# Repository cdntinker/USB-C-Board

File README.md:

# The NerdMage Rabbit Stack  Project

**_This project Will likely ALWAYS be a WIP._**

Do keep in mind that, because this project is continuously evolving, it'd be a very good idea to verify that any board you have an interest in is complete enough to meet your needs BEFORE having it fabbed.

The basic concept is a USB-C PD-capable power input section for various projects.  The initial board design & format is based on an ongoing project where 34x34mm is the maximum available space for this portion of the design.

In fact, the first USB power board for that project was 35x26mm & a photo of it is [in the Pix folder here](Pix/The-Original.png).  You can see that it was a very minimal USB-C to 3v3 power supply.

Now...

Many rabbit-holes later...

Many, many rabbit-holes later...

Things may be getting a little out of hand...

---

## 2023/09/29
Redesignating this repo from "USB-C-Board" to "The NerdMage Rabbit Stack".

## 2024/03/01
Re-arranging the hardware files for better clarity.

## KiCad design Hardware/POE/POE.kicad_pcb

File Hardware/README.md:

# The NerdMage Rabbit Stack  Project

* KiCAD Customs
  * Customised symbols, footprints & 3D models for KiCAD
* 3D
  * 3D render models & such
  * (I use FreeCAD here...)
* `___`
  * **Prototype.***
    * a copy of Prototype tucked away to make renaming simpler
    * (rename the files inside the folder, then ***COPY*** them out to the Hardware folder)
  * **zzzzzz.kicad_pcb**
    * A silkscreen layout aid
  * **zzzzzz.kicad_sch**
    * A schematic layout aid

---

* **Prototype**
  * Just a blank board with footprints in place to match up with the others.
* **USB-PD Board**
  * The Power Delivery Sink board
  * This board talks to the USB-C PD source & tells it what voltage/current is needed.
  * Options have been left in to just populate for non-PD usage as well.
  * It also contains a 3v3 regulator to either drive the controller board or supply your project.
* **Controller-8285**
  * A controller to tell the USB-PD Board what to request from the source.
  * (This one could also become a general usage ESP board... hhhmmm...)
* **Controller-RP2040**
  * Workin' on an RP2040-based controller board
* **Controller-Tarduino Clone**
  * An Atmega328-based controller board
  * (roughly based on an Arduino Pro-mini)
* **Programmer**
  * A CH340-based programmer board intended to sit on top of _Controller-8285_ or _Tarduino Clone_
* **Ethernet**
  * SPI Ethernet connectivity based on the W5500 chip
* **Ethernet-Spacer**
  * A placeholder board to make space in the stack for Ethernet jack
* **POE**
  * IEEE802.3af POE based on the Silvertel Ag9900 module
* **POE Spacer**
  * A placeholder board to make space in the stack for the Ag9900 module
* **Random Vreg**
  * Just a random voltage regulator board
  * Proof of concept really...
  * But then again...
* **USB Hub**
  * A 3-port USB Hub based on the TUSB2036
  * Downstream port 1 is set up to feed next board up in the stack.
* **Li-Ion Charger**
  * A 2s lithium battery charger
* **Li-Ion BMS**
  * A 2s lithium battery manager

There will, from time to time, appear more boards...

## Some future thoughts...

* Other MCUs
* Battery Charger
* BMS
* Display driver
* Inputs...
* I/O expansion
* Audio
* etc...etc...etc...

# Some notes about J7
(Yes, I know that J7 on all the boards is a bit of a mongrel...  Workin' on that...)

The purpose of J7 was initially to provide extra control signals between the PD board & the controller board.  As the PD board is managed via I2C, this may be un needed.

If so, then the connector should be available for SPI.  (ATM, The Ethernet board is using it as such.)

## A note about using SPI on J7
As SPI requires a separate select line (SCS) for each SPI device, this means that you can only have a single SPI device.  I am currently thinking about the idea of eliminating DEV-IO on pin 7 & designing some sort of 2-bit selection system using pins 7 & 8.

Another option might be to enforce placement of the feedthrough headers for J9 instead of copying I2C into J7.  This would give an option of a 3 or 4 bit selection system.

Must still put more thought into this...

# Notes
## 2023/09/26
Reworked *EVERYTHING* to 1.27mm headers & sockets to make stacking actually work.

## 2023/10/03
Changing J7 to dedicated I2C + SPI interface (well... Plus device reset & possibly 1 spare I/O...)

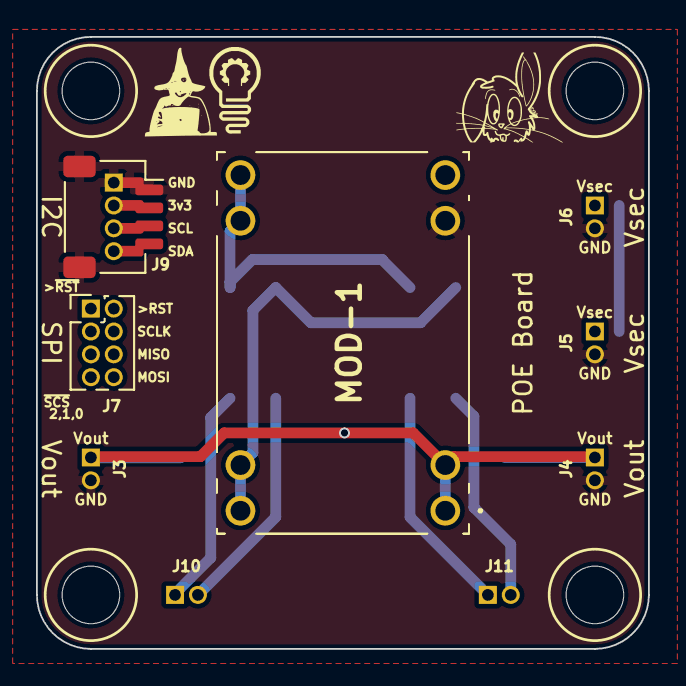
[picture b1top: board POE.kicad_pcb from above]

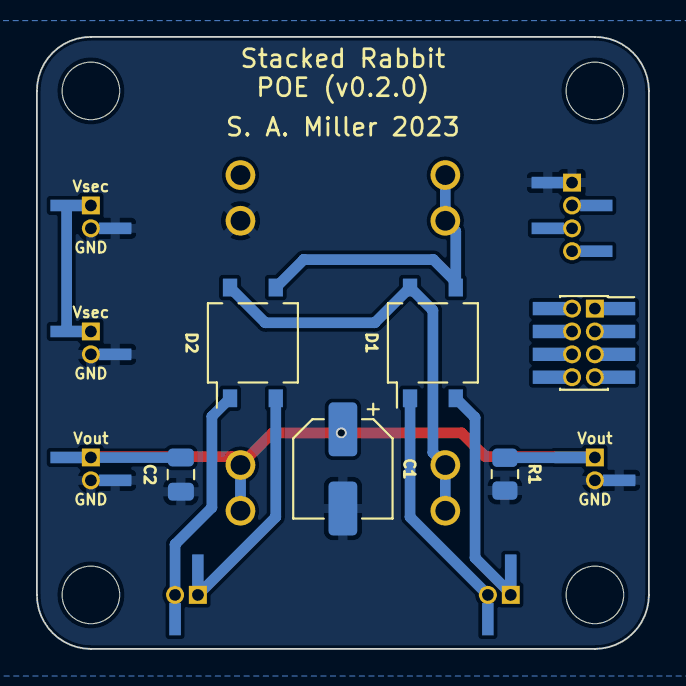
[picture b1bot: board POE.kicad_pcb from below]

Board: 2 copper layers, 34.0 x 34.0 mm, 14 parts (5 on the bottom side), 9 nets.

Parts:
C1: 100uf; CP_Elec_5x3
C2: 10uf; C_0805_2012Metric
D1, D2: MB4S; TO-269AA
J3, J4, J5, J6, J10, J11: Conn_01x02_Male; Board_Stacker_2
J7: Conn_01x08_Male; PinHeader_2x04_P1.27mm_Vertical
J9: QWIIC_Stackable; QWIIC_Stack_II
MOD-1: Ag9912LP
R1: R; R_0805_2012Metric

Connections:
GND: C1.2, C2.2, J3.2, J4.2, J5.2, J6.2, J9.1, J9.MP (MountPin), MOD-1.3 (-VDC), R1.2
VA1: D2.2, J11.1
VA2: D2.1, J11.2
VB1: D1.2, J10.1
VB2: D1.1, J10.2
Vin+: D1.3 (+), D2.3 (+), MOD-1.5 (VIN+_1), MOD-1.6 (VIN+_2)
Vin-: D1.4 (-), D2.4 (-), MOD-1.7 (VIN-_1), MOD-1.8 (VIN-_2)
Vout: C1.1, C2.1, J3.1, J4.1, MOD-1.1 (+VDC_1), MOD-1.2 (+VDC_2), R1.1
Vsec: J5.1, J6.1

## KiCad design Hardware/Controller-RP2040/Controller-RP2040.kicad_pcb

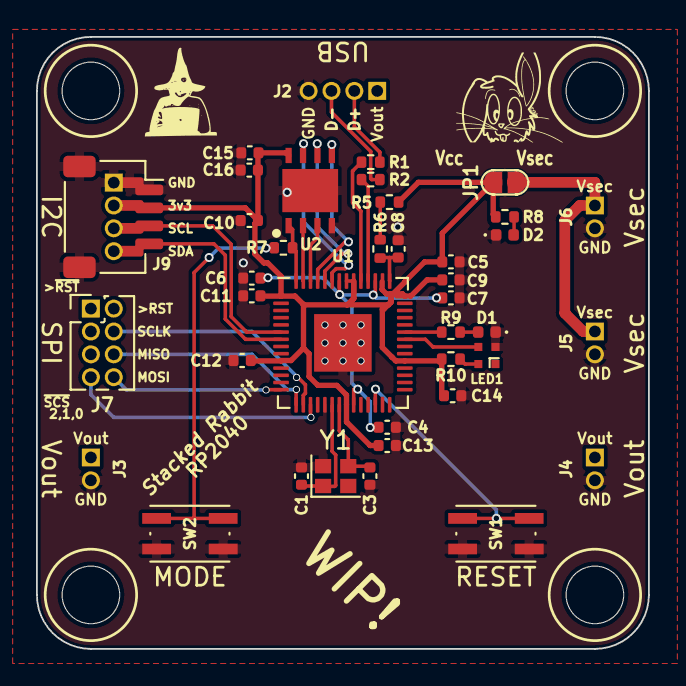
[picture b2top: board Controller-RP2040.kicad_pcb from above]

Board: 2 copper layers, 34.0 x 34.0 mm, 39 parts (0 on the bottom side), 31 nets.

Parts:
C1, C3: 20p; C_0402_1005Metric
C4, C5, C8, C15: 2u2; C_0402_1005Metric
C6, C7, C9, C10, C11, C12, C13, C14, C16: 100n; C_0402_1005Metric
D1, D2: LED; LED_0402_1005Metric
J2: Conn_01x04_Male; Board_Stacker_4
J3, J4, J5, J6: Conn_01x02_Male; Board_Stacker_2
J7: Conn_01x08_Male; PinHeader_2x04_P1.27mm_Vertical
J9: QWIIC_Stack_II
JP1: SolderJumper_2_Open; SolderJumper-2_P_Open_Rounded_skinny
LED1: XL-1010RGBC-WS2812B; XL1010RGBCWS2812B
R1, R2: 27; R_0402_1005Metric
R5: 200; R_0402_1005Metric
R6: 1; R_0402_1005Metric
R7: 1k; R_0402_1005Metric
R8: 2k2; R_0402_1005Metric
R9: 470; R_0402_1005Metric
R10: ???; R_0402_1005Metric
SW1, SW2: SW_Push; SW_Push_TS273014TP
U1: RP2040; QFN-56-1EP_7x7mm_P0.4mm_EP3.2x3.2mm
U2: W25Q32JVXGIQ; SON80P400X400X50-9N
Y1: 12MHz; Crystal_SMD_2016-4Pin_2.0x1.6mm

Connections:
+1V1: C4.2, C6.1, C7.1, U1.23 (DVDD), U1.45 (VREG_VOUT), U1.50 (DVDD)
+3V3: C5.1, C9.1, C10.1, C11.1, C12.1, C13.1, C14.1, C15.2, C16.1, J9.2, JP1.2 (B), R5.2, R8.1, R10.1, U1.1 (IOVDD), U1.10 (IOVDD), U1.22 (IOVDD), U1.33 (IOVDD), U1.42 (IOVDD), U1.44 (VREG_IN), U1.48 (USB_VDD), U1.49 (IOVDD), U2.8 (VCC)
/USB_DM: R2.2, U1.46 (USB_DM)
/USB_DP: R1.2, U1.47 (USB_DP)
/Xout: C3.1, U1.21 (XOUT), Y1.3
ADC_REF: R5.1, R6.2
BootMode: R7.2, SW2.2
GND: C1.2, C3.2, C4.1, C5.2, C6.2, C7.2, C8.1, C9.2, C10.2, C11.2, C12.2, C13.2, C14.2, C15.1, C16.2, D1.1 (K), D2.1 (K), J2.4, J3.2, J4.2, J5.2, J6.2, J9.1, J9.MP (MountPin), LED1.3 (GND), SW1.1, SW2.1, U1.19 (TESTEN), U1.57 (GND), U2.4 (GND), U2.9 (EP), Y1.4
MISO: J7.6, U1.15 (GPIO12)
MOSI: J7.8, U1.14 (GPIO11)
unnamed: C1.1, U1.20 (XIN), Y1.1
unnamed: C8.2, R6.1, U1.43 (ADC_AVDD)
unnamed: D1.2 (A), R9.2
unnamed: D2.2 (A), R8.2
unnamed: LED1.2 (VDD), R10.2
QSPI SS: R7.1, U1.56 (QSPI_SS), U2.1 (~CS)
QSPI_SCLK: U1.52 (QSPI_SCLK), U2.6 (CLK)
QSPI_SD0: U1.53 (QSPI_SD0), U2.5 (DI(IO0))
QSPI_SD1: U1.55 (QSPI_SD1), U2.2 (DO(IO1))
QSPI_SD2: U1.54 (QSPI_SD2), U2.3 (IO2)
QSPI_SD3: U1.51 (QSPI_SD3), U2.7 (IO3)
Reset: SW1.2, U1.26 (RUN)
SCL: J9.4, U1.7 (GPIO5)
SCLK: J7.4, U1.16 (GPIO13)
SDA: J9.3, U1.6 (GPIO4)
UD+: J2.2, R1.1
UD-: J2.3, R2.1
Vsec: J5.1, J6.1, JP1.1 (A)
io14: J7.7, U1.17 (GPIO14)
io24: LED1.4 (DI), U1.36 (GPIO24)
io25: R9.1, U1.37 (GPIO25)

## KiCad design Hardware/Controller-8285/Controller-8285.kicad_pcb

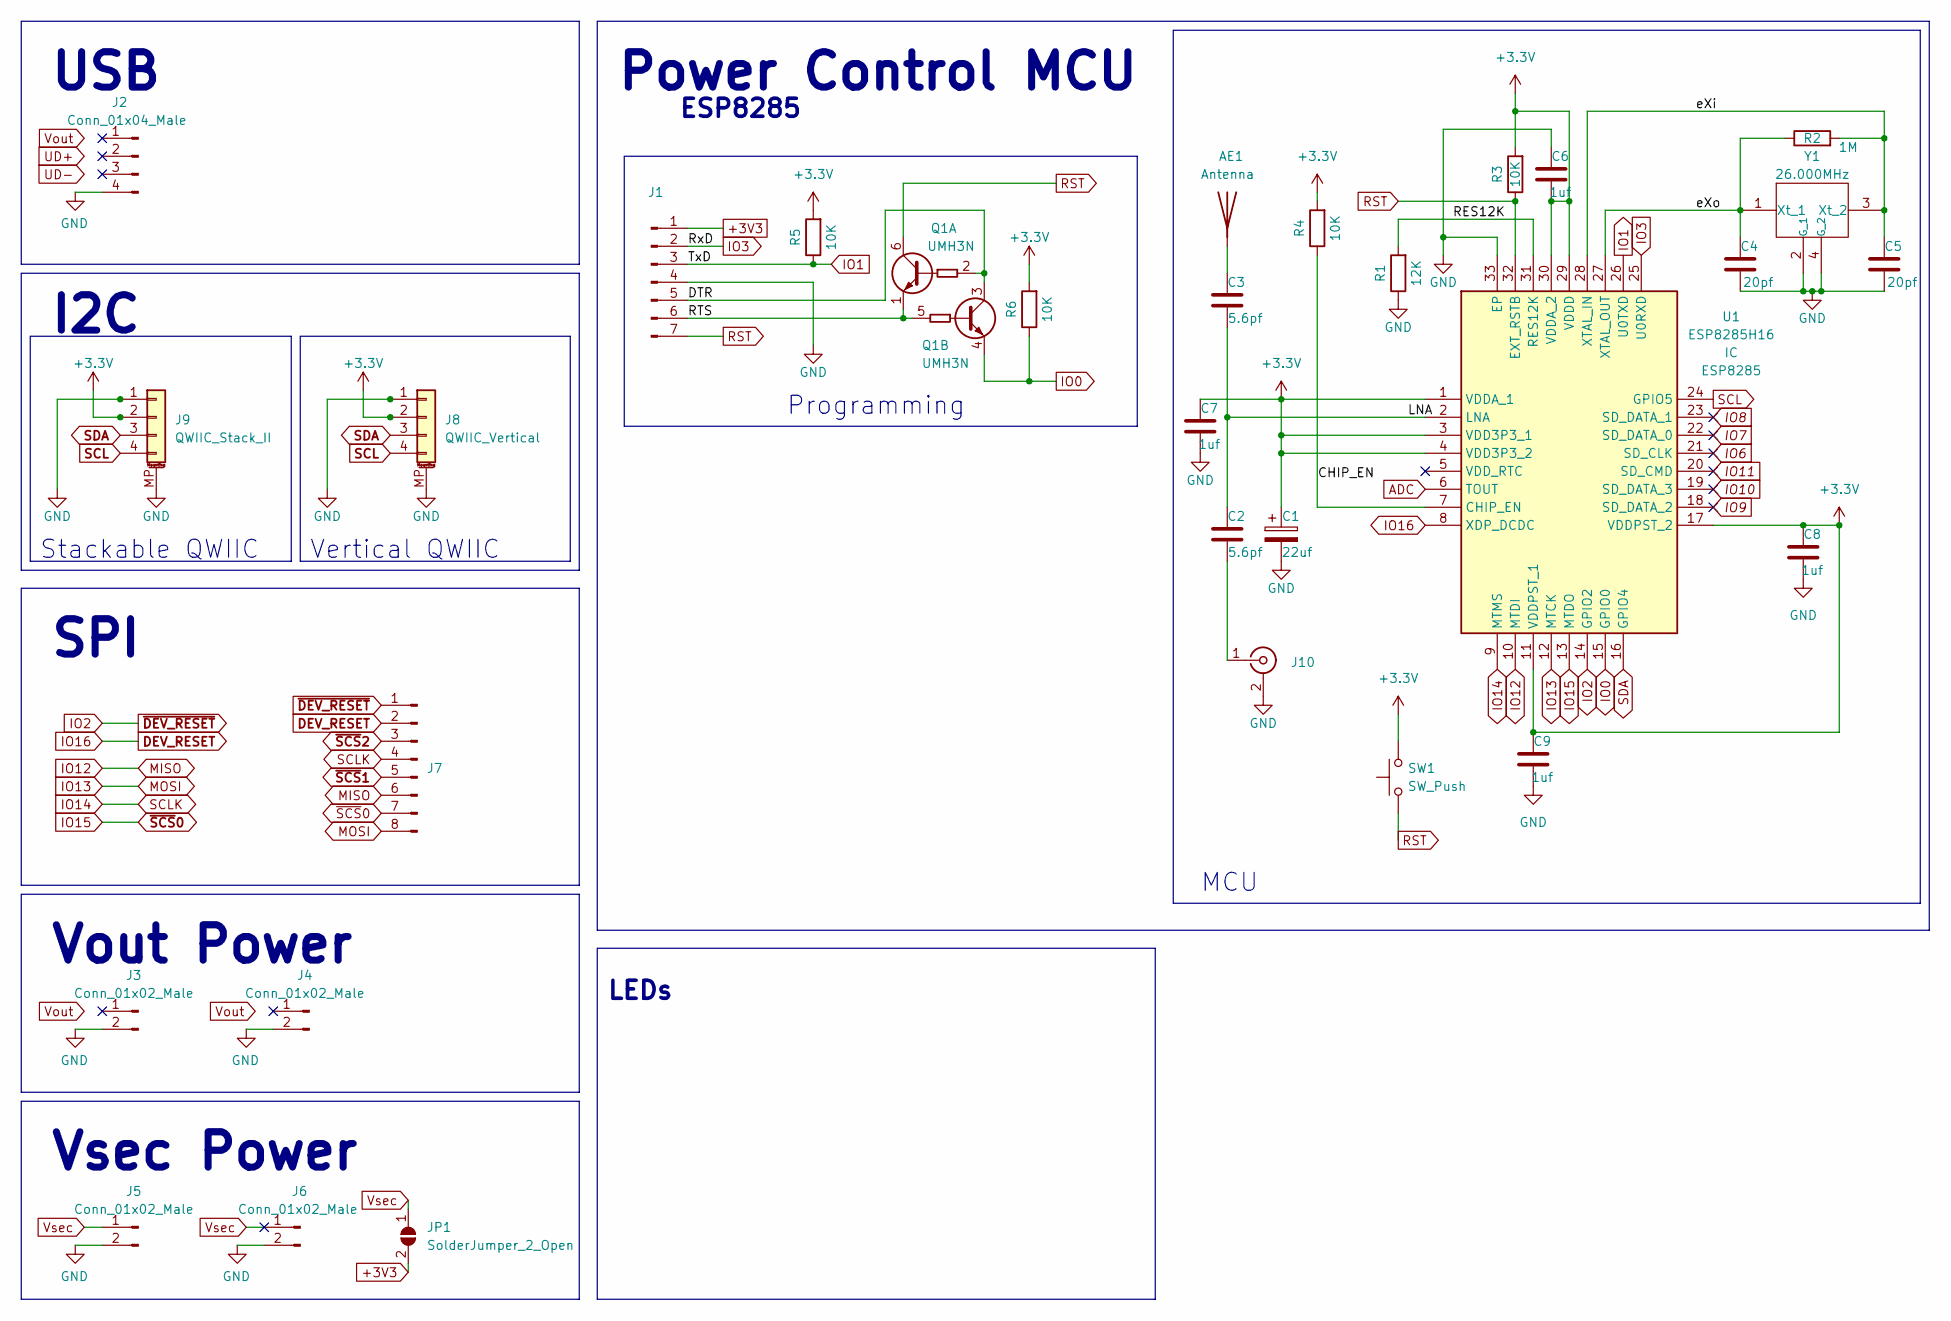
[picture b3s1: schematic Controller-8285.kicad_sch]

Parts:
AE1: Antenna; Texas_SWRA117D_2.4GHz_Left
C1: 22uf; CP_EIA-6032-28-Tantalumm_HandSolder; LCSC C89246
C2, C3: 5.6pf; C_0603_1608Metric; LCSC C162238
C4, C5: 20pf; C_0603_1608Metric; LCSC C325469
C6, C7, C8, C9: 1uf; C_0603_1608Metric; LCSC C559769
J1: Conn_01x07_Male; Board_Stacker_7
J2: Conn_01x04_Male; Board_Stacker_4
J3, J4, J5, J6: Conn_01x02_Male; Board_Stacker_2
J7: Conn_01x08_Male; PinHeader_2x04_P1.27mm_Vertical; LCSC C2881786 + C2684732
J8: QWIIC_Vertical; LCSC C145961
J9: QWIIC_Stack_II; LCSC C145956, C2881513, C2938401
J10: Conn_Coaxial; U.FL_Molex_MCRF_73412-0110_Vertical; LCSC C88373
JP1: SolderJumper_2_Open; SolderJumper-2_P_Open_Rounded_skinny
Q1: UMH3N; SOT-363_SC-70-6; LCSC C62892
R1: 12K; R_0603_1608Metric; LCSC C22790
R2: 1M; R_0603_1608Metric; LCSC C22935
R3, R4, R5, R6: 10K; R_0603_1608Metric; LCSC C25804
SW1: SW_Push; SW_Push_TS273014TP; LCSC C2858276
U1: ESP8285H16; QFN50P500X500X90-33N-D; Manufacturer_Part_Number ESP8285; LCSC C967019
Y1: 26.000MHz; ABM825000MHz10B1UT; LCSC C2149083

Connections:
/CHIP_EN: R4.1, U1.7 (CHIP_EN)
/DTR: J1.5, Q1.2 (B1), Q1.3 (C2)
/LNA: C2.1, C3.1, U1.2 (LNA)
/RES12K: R1.2, U1.31 (RES12K)
/RTS: J1.6, Q1.1 (E1), Q1.5 (B2)
/eXi: C5.2, R2.2, U1.28 (XTAL_IN), Y1.3 (Xt_2)
/eXo: C4.2, R2.1, U1.27 (XTAL_OUT), Y1.1 (Xt_1)
ADC: U1.6 (TOUT)
DEV_RESET: J7.2, U1.8 (XDP_DCDC)
GND: C1.2, C4.1, C5.1, C6.1, C7.1, C8.1, C9.1, J1.4, J2.4, J3.2, J4.2, J5.2, J6.2, J8.1, J8.MP (MountPin), J9.1, J9.MP (MountPin), J10.2 (Ext), R1.1, U1.33 (EP), Y1.2 (G_1), Y1.4 (G_2)
IO0: Q1.4 (E2), R6.1, U1.15 (GPIO0)
IO1: J1.3, R5.1, U1.26 (U0TXD)
IO2: J7.1, U1.14 (GPIO2)
IO3: J1.2, U1.25 (U0RXD)
IO6: U1.21 (SD_CLK)
IO7: U1.22 (SD_DATA_0)
IO8: U1.23 (SD_DATA_1)
IO9: U1.18 (SD_DATA_2)
IO10: U1.19 (SD_DATA_3)
IO11: U1.20 (SD_CMD)
IO12: J7.6, U1.10 (MTDI)
IO13: J7.8, U1.12 (MTCK)
IO14: J7.4, U1.9 (MTMS)
IO15: J7.7, U1.13 (MTDO)
unnamed: AE1.1, C3.2
unnamed: C2.2, J10.1 (In)
RST: J1.7, Q1.6 (C1), R3.1, SW1.1, U1.32 (EXT_RSTB)
SCL: J8.4, J9.4, U1.24 (GPIO5)
SDA: J8.3, J9.3, U1.16 (GPIO4)
Vsec: J5.1, J6.1, JP1.1 (A)
~SCS1: J7.5
~SCS2: J7.3

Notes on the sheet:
I2C
MCU
Vertical QWIIC
Vsec Power
ESP8285
Power Control MCU
USB
SPI
Programming
Vout Power
Stackable QWIIC
LEDs

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
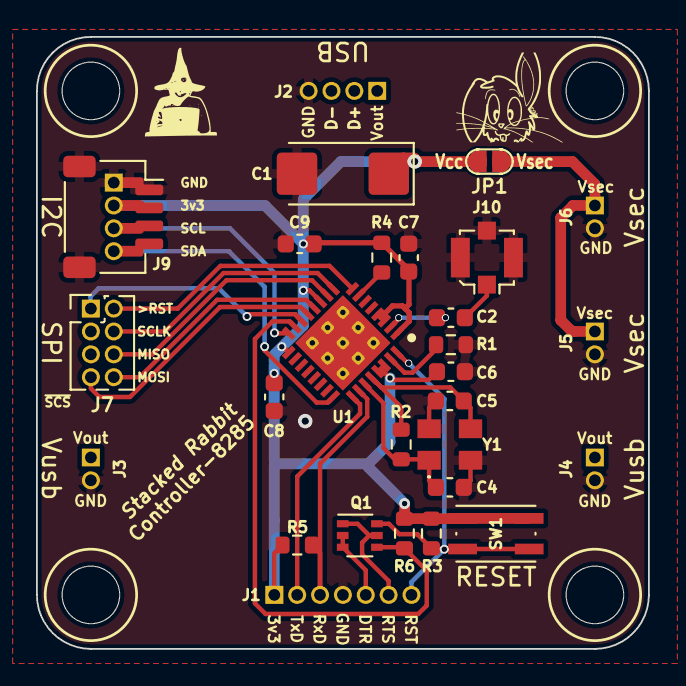
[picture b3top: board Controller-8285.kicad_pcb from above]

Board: 2 copper layers, 34.0 x 34.0 mm, 28 parts (0 on the bottom side), 23 nets.

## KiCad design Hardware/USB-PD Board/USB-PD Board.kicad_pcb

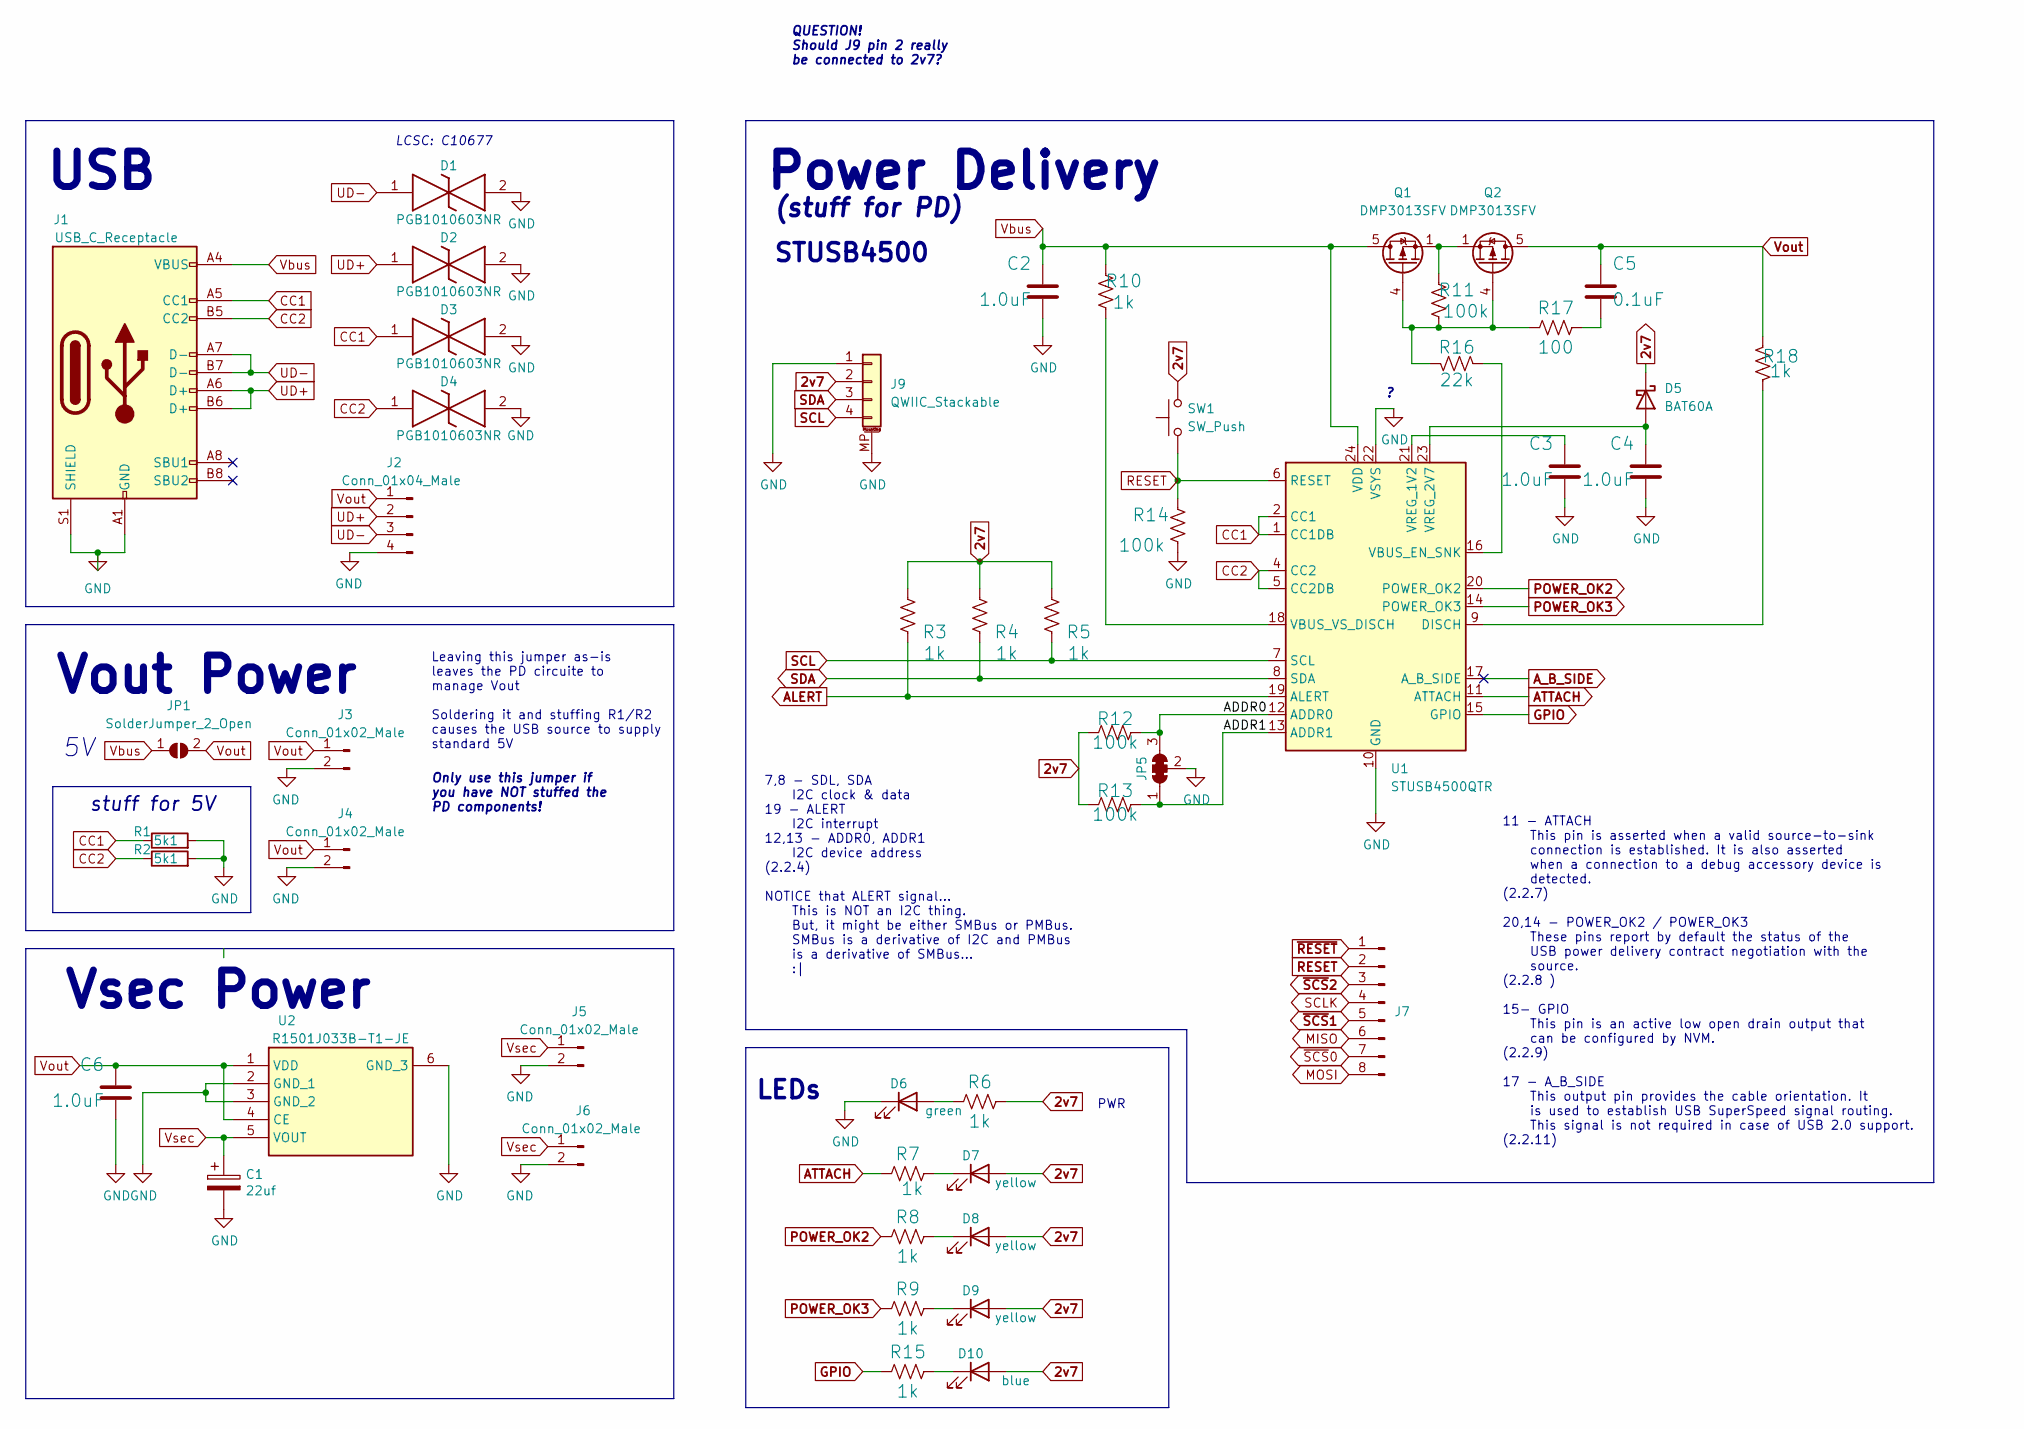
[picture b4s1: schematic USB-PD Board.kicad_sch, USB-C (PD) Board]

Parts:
C1: 22uf; CP_EIA-6032-28-Tantalumm_HandSolder; LCSC C145122
C2, C3, C4, C6: 1.0uF; C_0603_1608Metric; LCSC C559769
C5: 0.1uF; C_0603_1608Metric; LCSC C14663
D1, D2, D3, D4: PGB1010603NR; PGB1010603NRHF; Manufacturer_Part_Number PGB1010603NR; Mouser Part Number 576-PGB1010603NR
D5: BAT60A; D_SOD-323; LCSC C5355496
D6: green; LED_0603_1608Metric; LCSC C434420
D7: yellow; LED_0603_1608Metric; LCSC C434421
D8, D9: yellow; LED_0603_1608Metric; LCSC C434424
D10: blue; LED_0603_1608Metric; LCSC C434420
J1: USB_C_Receptacle; USB_C_Receptacle_HRO_TYPE-C-31-M-12; LCSC C2765186
J2: Conn_01x04_Male; Board_Stacker_4
J3, J4, J5, J6: Conn_01x02_Male; Board_Stacker_2
J7: Conn_01x08_Male; PinHeader_2x04_P1.27mm_Vertical; LCSC C2881786 + C2684732
J9: QWIIC_Stackable; QWIIC_Stack_II
JP1: SolderJumper_2_Open; SolderJumper-2_P_Open_Rounded_skinny
JP5: SolderJumper_3_Bridged123; SolderJumper-3_P1.3mm_Bridged123_Pad1.0x1.5mm
Q1, Q2: DMP3013SFV; Diodes_PowerDI3333-8; LCSC C264098
R1, R2: 5k1; R_0603_1608Metric_Pad0.98x0.95mm_HandSolder; LCSC C23186
R3, R4, R5, R6, R7, R8, R9, R10, R15, R18: 1k; R_0603_1608Metric; LCSC C21190
R11, R12, R13, R14: 100k; R_0603_1608Metric; LCSC C25803
R16: 22k; R_0603_1608Metric; LCSC C31850
R17: 100; R_0603_1608Metric; LCSC C22775
SW1: SW_Push; SW_Push_TS273014TP; LCSC C2858276
U1: STUSB4500QTR; QFN-24-1EP_4x4mm_P0.5mm_EP2.7x2.7mm; LCSC C2678061
U2: R1501J033B-T1-JE; R1501J033BT1JE; Manufacturer_Part_Number R1501J033B-T1-JE; LCSC C3748149

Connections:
2v7: D5.1 (K), D7.2 (A), D8.2 (A), D9.2 (A), D10.2 (A), J9.2, R3.2, R4.2, R5.2, R6.2, R12.2, R13.2, SW1.2
/ADDR0: JP5.3 (B), R12.1, U1.12 (ADDR0)
/ADDR1: JP5.1 (A), R13.1, U1.13 (ADDR1)
ALERT: R3.1, U1.19 (ALERT)
ATTACH: R7.1, U1.11 (ATTACH)
A_B_SIDE: U1.17 (A_B_SIDE)
CC1: D3.1, J1.A5 (CC1), R1.1, U1.1 (CC1DB), U1.2 (CC1)
CC2: D4.1, J1.B5 (CC2), R2.1, U1.4 (CC2), U1.5 (CC2DB)
GND: C1.2, C2.2, C3.2, C4.2, C6.2, D1.2, D2.2, D3.2, D4.2, D6.1 (K), J1.A1 (GND), J1.A12 (GND), J1.B1 (GND), J1.B12 (GND), J1.S1 (SHIELD), J2.4, J3.2, J4.2, J5.2, J6.2, J9.1, J9.MP (MountPin), JP5.2 (C), R1.2, R2.2, R14.1, U1.10 (GND), U1.22 (VSYS), U1.25 (GND), U2.2 (GND_1), U2.3 (GND_2), U2.6 (GND_3)
GPIO: R15.1, U1.15 (GPIO)
MISO: J7.6
MOSI: J7.8
unnamed: C3.1, U1.21 (VREG_1V2)
unnamed: C4.1, D5.2 (A), U1.23 (VREG_2V7)
unnamed: C5.2, R17.2
unnamed: D6.2 (A), R6.1
unnamed: D7.1 (K), R7.2
unnamed: D8.1 (K), R8.2
unnamed: D9.1 (K), R9.2
unnamed: D10.1 (K), R15.2
unnamed: Q1.1 (S), Q1.2 (S), Q1.3 (S), Q2.1 (S), Q2.2 (S), Q2.3 (S), R11.2
unnamed: Q1.4 (G), Q2.4 (G), R11.1, R16.1, R17.1
unnamed: R10.1, U1.18 (VBUS_VS_DISCH)
unnamed: R16.2, U1.16 (VBUS_EN_SNK)
unnamed: R18.2, U1.9 (DISCH)
POWER_OK2: R8.1, U1.20 (POWER_OK2)
POWER_OK3: R9.1, U1.14 (POWER_OK3)
RESET: J7.2, R14.2, SW1.1, U1.6 (RESET)
SCL: J9.4, R5.1, U1.7 (SCL)
SCLK: J7.4
SDA: J9.3, R4.1, U1.8 (SDA)
UD+: D2.1, J1.A6 (D+), J1.B6 (D+), J2.2
UD-: D1.1, J1.A7 (D-), J1.B7 (D-), J2.3
Vbus: C2.1, J1.A4 (VBUS), J1.A9 (VBUS), J1.B4 (VBUS), J1.B9 (VBUS), JP1.1 (A), Q1.5 (D), R10.2, U1.24 (VDD)
Vout: C5.1, C6.1, J2.1, J3.1, J4.1, JP1.2 (B), Q2.5 (D), R18.1, U2.1 (VDD), U2.4 (CE)
Vsec: C1.1, J5.1, J6.1, U2.5 (VOUT)
~RESET: J7.1
~SCS0: J7.7
~SCS1: J7.5
~SCS2: J7.3

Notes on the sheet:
Vsec Power
Vout Power
Only use this jumper if you have NOT stuffed the PD components!
QUESTION! Should J9 pin 2 really be connected to 2v7?
stuff for 5V
STUSB4500
LCSC: C10677
USB
7,8 - SDL, SDA I2C clock & data 19 - ALERT I2C interrupt 12,13 - ADDR0, ADDR1 I2C device address (2.2.4) NOTICE that ALERT signal... This is NOT an I2C thing. But, it might be either SMBus or PMBus. SMBus is a derivative of I2C and PMBus is a derivative of SMBus... :|
(stuff for PD)
Power Delivery
Leaving this jumper as-is leaves the PD circuite to manage Vout Soldering it and stuffing R1/R2 causes the USB source to supply standard 5V
PWR
11 - ATTACH This pin is asserted when a valid source-to-sink connection is established. It is also asserted when a connection to a debug accessory device is detected. (2.2.7) 20,14 - POWER_OK2 / POWER_OK3 These pins report by default the status of the USB power delivery contract negotiation with th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
LEDs

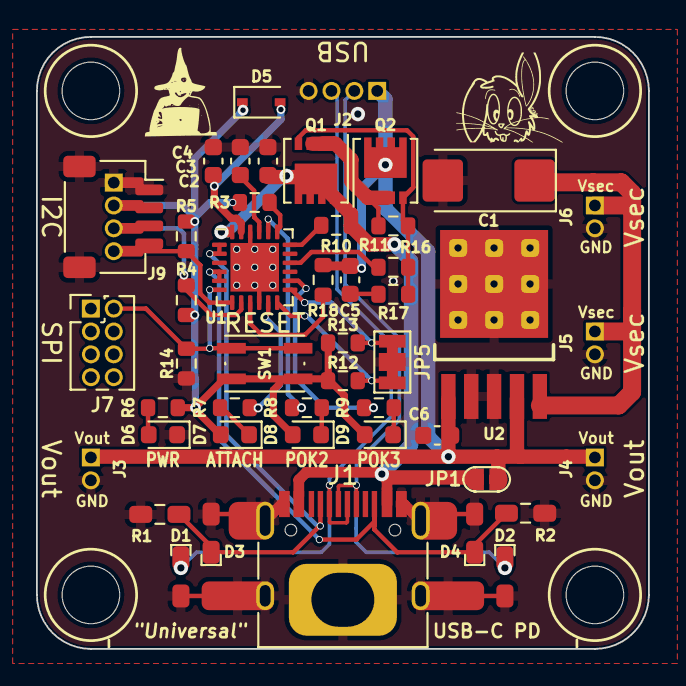
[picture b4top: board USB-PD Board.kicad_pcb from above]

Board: 2 copper layers, 34.0 x 34.0 mm, 47 parts (0 on the bottom side), 30 nets.

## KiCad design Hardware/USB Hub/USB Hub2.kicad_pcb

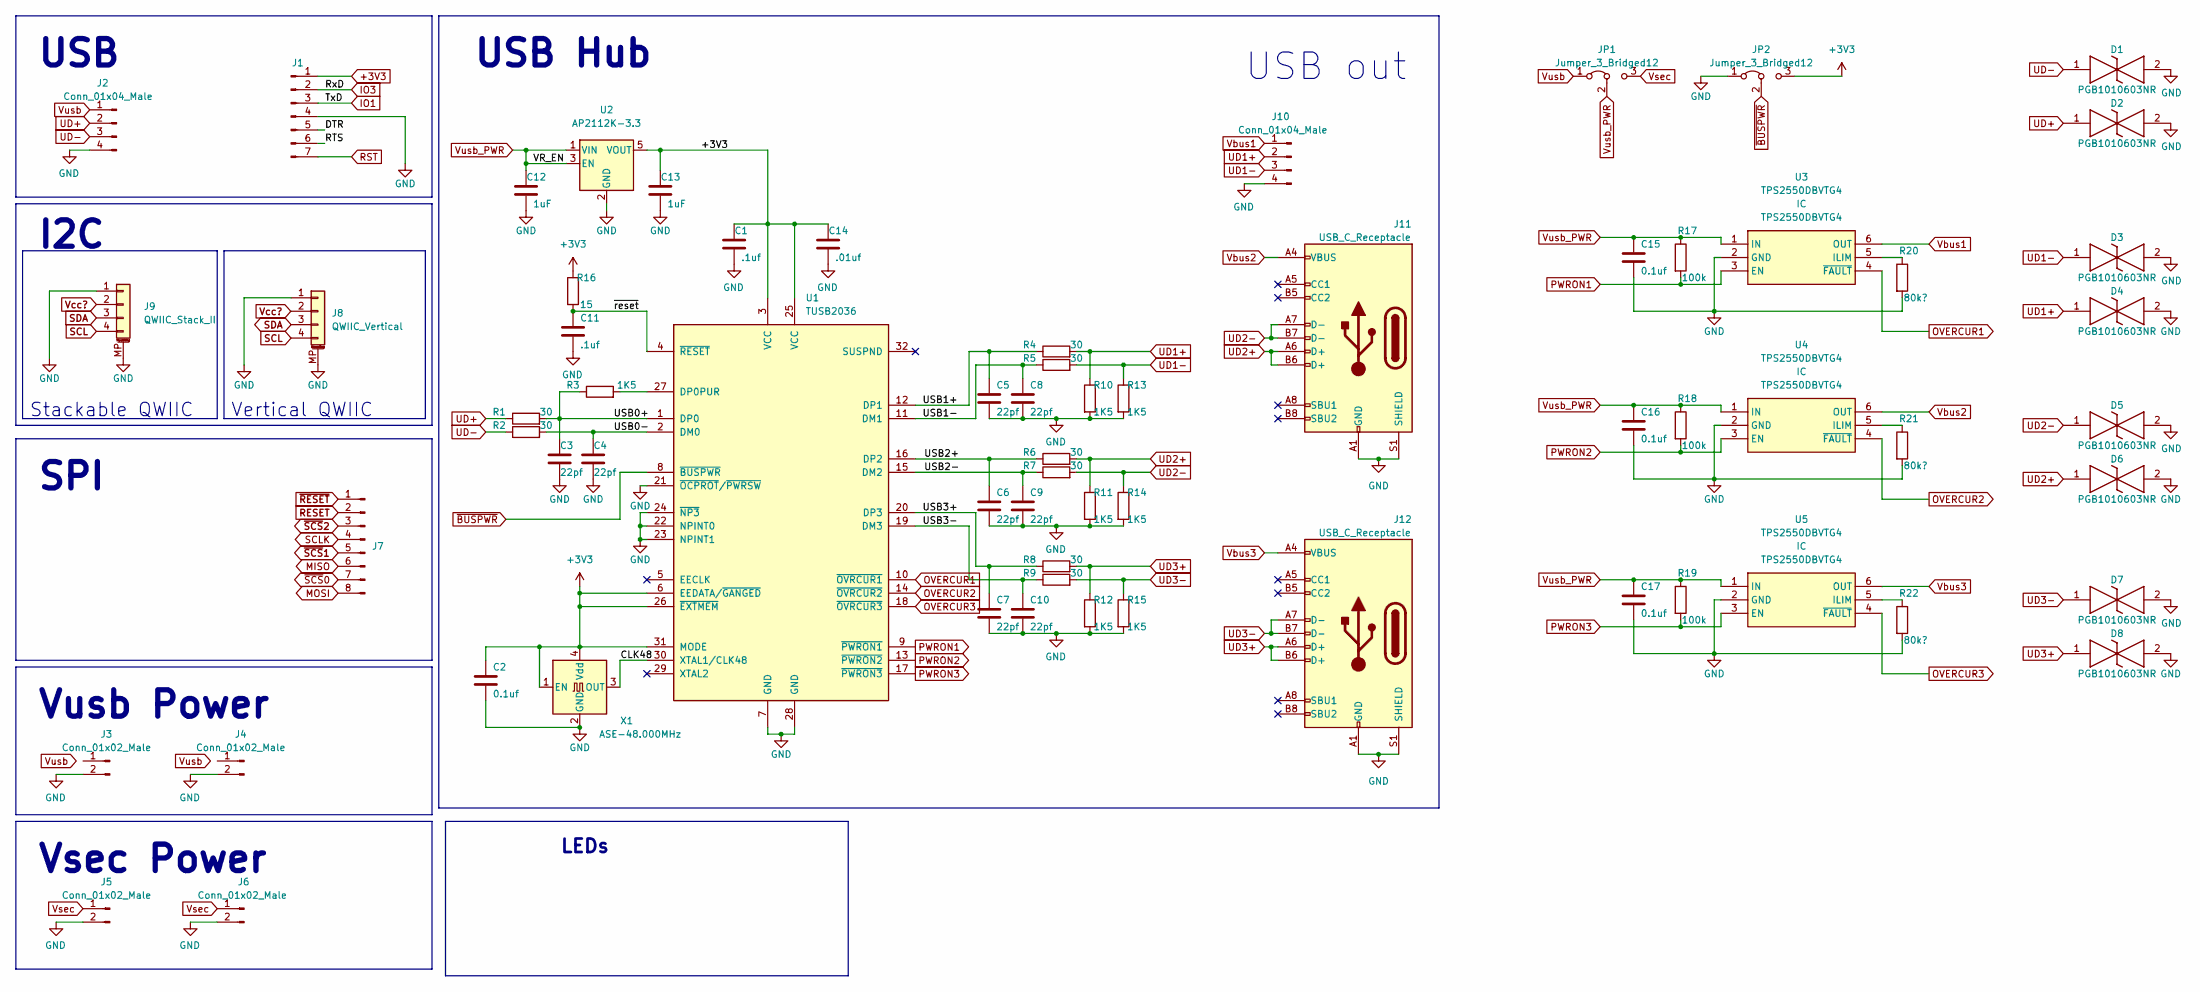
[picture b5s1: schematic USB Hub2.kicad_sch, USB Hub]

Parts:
C1, C11: .1uf; C_0603_1608Metric
C2, C15, C16, C17: 0.1uf; C_0603_1608Metric
C3, C4, C5, C6, C7, C8, C9, C10: 22pf; C_0603_1608Metric
C12, C13: 1uF; C_0603_1608Metric
C14: .01uf; C_0603_1608Metric
D1, D2, D3, D4, D5, D6, D7, D8: PGB1010603NR; PGB1010603NRHF; Manufacturer_Part_Number PGB1010603NR; Mouser Part Number 576-PGB1010603NR
J1: Conn_01x07_Male; Board_Stacker_7
J2: Conn_01x04_Male; PinSocket_1x04_P1.27mm_Vertical_SMD_Pin1Left; LCSC C2938401 + C2881513
J3, J4, J5, J6: Conn_01x02_Male; Board_Stacker_2; LCSC C2938400 + C2881511
J7: Conn_01x08_Male; PinHeader_2x04_P1.27mm_Vertical; LCSC C2881786 + C2684732
J8: QWIIC_Vertical; LCSC C145961
J9: QWIIC_Stack_II; LCSC C145956 + C2938401 + C2881513
J10: Conn_01x04_Male; PinHeader_1x04_P1.27mm_Vertical_SMD_Pin1Right
J11, J12: USB_C_Receptacle; USB_C_Receptacle_HRO_TYPE-C-NARROW; LCSC C2765186
JP1: Jumper_3_Bridged12; SolderJumper-3_P1.3mm_Bridged2Bar12_RoundedPad1.0x1.5mm
JP2: Jumper_3_Bridged12; SolderJumper-3_P1.3mm_Bridged12_RoundedPad1.0x1.5mm
R1, R2, R4, R5, R6, R7, R8, R9: 30; R_0603_1608Metric
R3, R10, R11, R12, R13, R14, R15: 1K5; R_0603_1608Metric
R16: 15; R_0603_1608Metric
R17, R18, R19: 100k; R_0603_1608Metric
R20, R21, R22: 80k?; R_0603_1608Metric
U1: TUSB2036; LQFP-32_7x7mm_P0.8mm
U2: AP2112K-3.3; SOT-23-5; LCSC C51118
U3, U4, U5: TPS2550DBVTG4; SOT-23-6; Manufacturer_Part_Number TPS2550DBVTG4; Mouser Part Number 595-TPS2550DBVTG4
X1: ASE-48.000MHz; Oscillator_SMD_Abracon_ASE-4Pin_3.2x2.5mm; LCSC C2650694

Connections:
+3V3: C1.1, C2.1, C13.1, C14.1, JP2.3 (B), R16.1, U1.3 (VCC), U1.6 (EEDATA/~GANGED), U1.25 (VCC), U1.26 (~EXTMEM), U1.31 (MODE), U2.5 (VOUT), X1.1 (EN), X1.4 (Vdd)
/CLK48: U1.30 (XTAL1/CLK48), X1.3 (OUT)
/USB0+: C3.1, R1.2, R3.1, U1.1 (DP0)
/USB0-: C4.1, R2.2, U1.2 (DM0)
/USB1+: C5.1, R4.1, U1.12 (DP1)
/USB1-: C8.1, R5.1, U1.11 (DM1)
/USB2+: C6.1, R6.1, U1.16 (DP2)
/USB2-: C9.1, R7.1, U1.15 (DM2)
/USB3+: C7.1, R8.1, U1.20 (DP3)
/USB3-: C10.1, R9.1, U1.19 (DM3)
/~reset: C11.1, R16.2, U1.4 (~RESET)
GND: C1.2, C2.2, C3.2, C4.2, C5.2, C6.2, C7.2, C8.2, C9.2, C10.2, C11.2, C12.2, C13.2, C14.2, C15.2, C16.2, C17.2, D1.2, D2.2, D3.2, D4.2, D5.2, D6.2, D7.2, D8.2, J1.4, J2.4, J3.2, J4.2, J5.2, J6.2, J8.1, J8.MP (MountPin), J9.1, J9.MP (MountPin), J10.4, J11.A1 (GND), J11.A12 (GND), J11.B1 (GND), J11.B12 (GND), J11.S1 (SHIELD), J12.A1 (GND), J12.A12 (GND), J12.B1 (GND), J12.B12 (GND), J12.S1 (SHIELD), JP2.1 (A), R10.2, R11.2, R12.2, R13.2, R14.2, R15.2, R20.2, R21.2, R22.2, U1.7 (GND), U1.21 (~OCPROT/~PWRSW), U1.22 (NPINT0), U1.23 (NPINT1), U1.24 (~NP3), U1.28 (GND), U2.2 (GND), U3.2 (GND), U4.2 (GND), U5.2 (GND), X1.2 (GND)
MISO: J7.6
MOSI: J7.8
unnamed: R3.2, U1.27 (DP0PUR)
unnamed: R20.1, U3.5 (ILIM)
unnamed: R21.1, U4.5 (ILIM)
unnamed: R22.1, U5.5 (ILIM)
OVERCUR1: U1.10 (~OVRCUR1), U3.4 (~FAULT)
OVERCUR2: U1.14 (~OVRCUR2), U4.4 (~FAULT)
OVERCUR3: U1.18 (~OVRCUR3), U5.4 (~FAULT)
PWRON1: R17.2, U1.9 (~PWRON1), U3.3 (EN)
PWRON2: R18.2, U1.13 (~PWRON2), U4.3 (EN)
PWRON3: R19.2, U1.17 (~PWRON3), U5.3 (EN)
RESET: J7.2
SCL: J8.4, J9.4
SCLK: J7.4
SDA: J8.3, J9.3
UD1+: D4.1, J10.2, R4.2, R10.1
UD1-: D3.1, J10.3, R5.2, R13.1
UD2+: D6.1, J11.A6 (D+), J11.B6 (D+), R6.2, R11.1
UD2-: D5.1, J11.A7 (D-), J11.B7 (D-), R7.2, R14.1
UD3+: D8.1, J12.A6 (D+), J12.B6 (D+), R8.2, R12.1
UD3-: D7.1, J12.A7 (D-), J12.B7 (D-), R9.2, R15.1
UD+: D2.1, J2.2, R1.1
UD-: D1.1, J2.3, R2.1
Vbus1: J10.1, U3.6 (OUT)
Vbus2: J11.A4 (VBUS), J11.A9 (VBUS), J11.B4 (VBUS), J11.B9 (VBUS), U4.6 (OUT)
Vbus3: J12.A4 (VBUS), J12.A9 (VBUS), J12.B4 (VBUS), J12.B9 (VBUS), U5.6 (OUT)
Vcc?: J8.2, J9.2
Vsec: J5.1, J6.1, JP1.3 (B)
Vusb: J2.1, JP1.1 (A)
Vusb_PWR: C12.1, C15.1, C16.1, C17.1, JP1.2 (C), R17.1, R18.1, R19.1, U2.1 (VIN), U2.3 (EN), U3.1 (IN), U4.1 (IN), U5.1 (IN)
~BUSPWR: JP2.2 (C), U1.8 (~BUSPWR)
~RESET: J7.1
~SCS0: J7.7
~SCS1: J7.5
~SCS2: J7.3

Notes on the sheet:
USB out
Vusb Power
I2C
Stackable QWIIC
SPI
Vsec Power
USB
USB Hub
Vertical QWIIC
LEDs

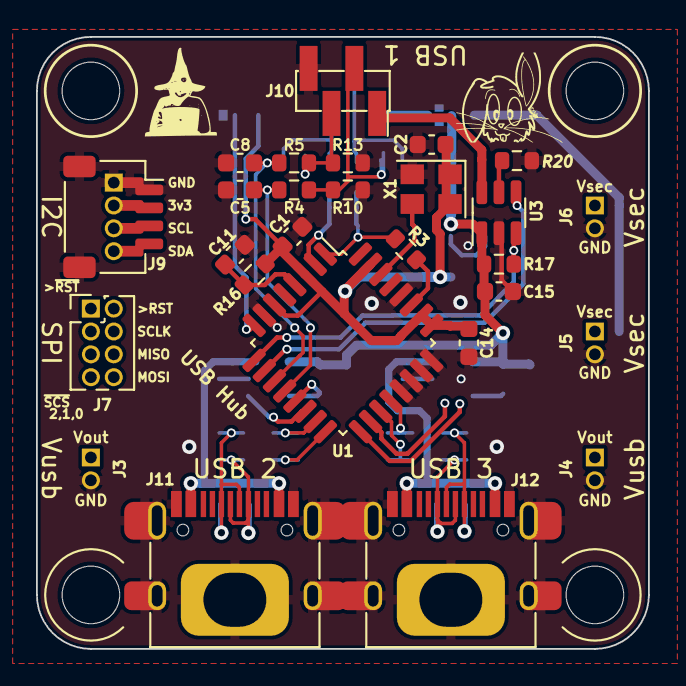
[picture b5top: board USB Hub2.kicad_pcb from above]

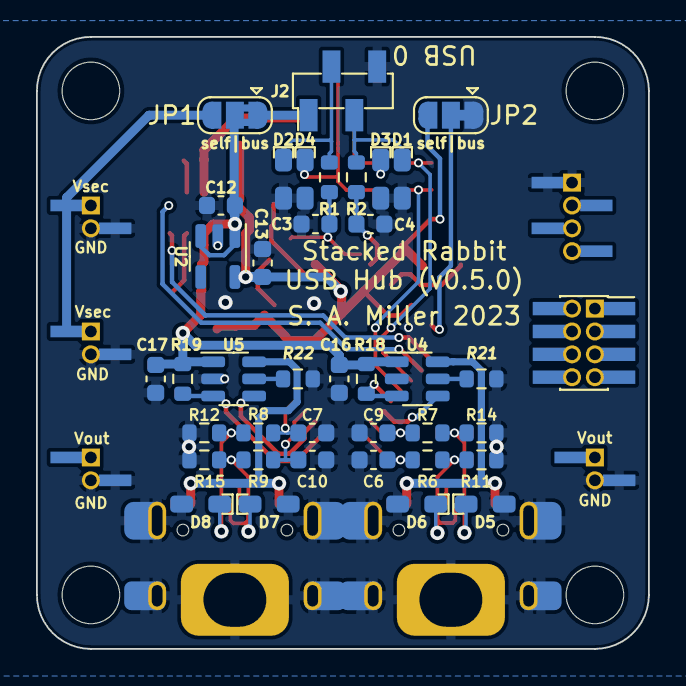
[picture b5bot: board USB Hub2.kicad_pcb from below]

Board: 2 copper layers, 34.0 x 34.0 mm, 65 parts (38 on the bottom side), 37 nets.
